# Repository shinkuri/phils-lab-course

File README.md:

# Learning PCB Design 
## Phil's Lab #11

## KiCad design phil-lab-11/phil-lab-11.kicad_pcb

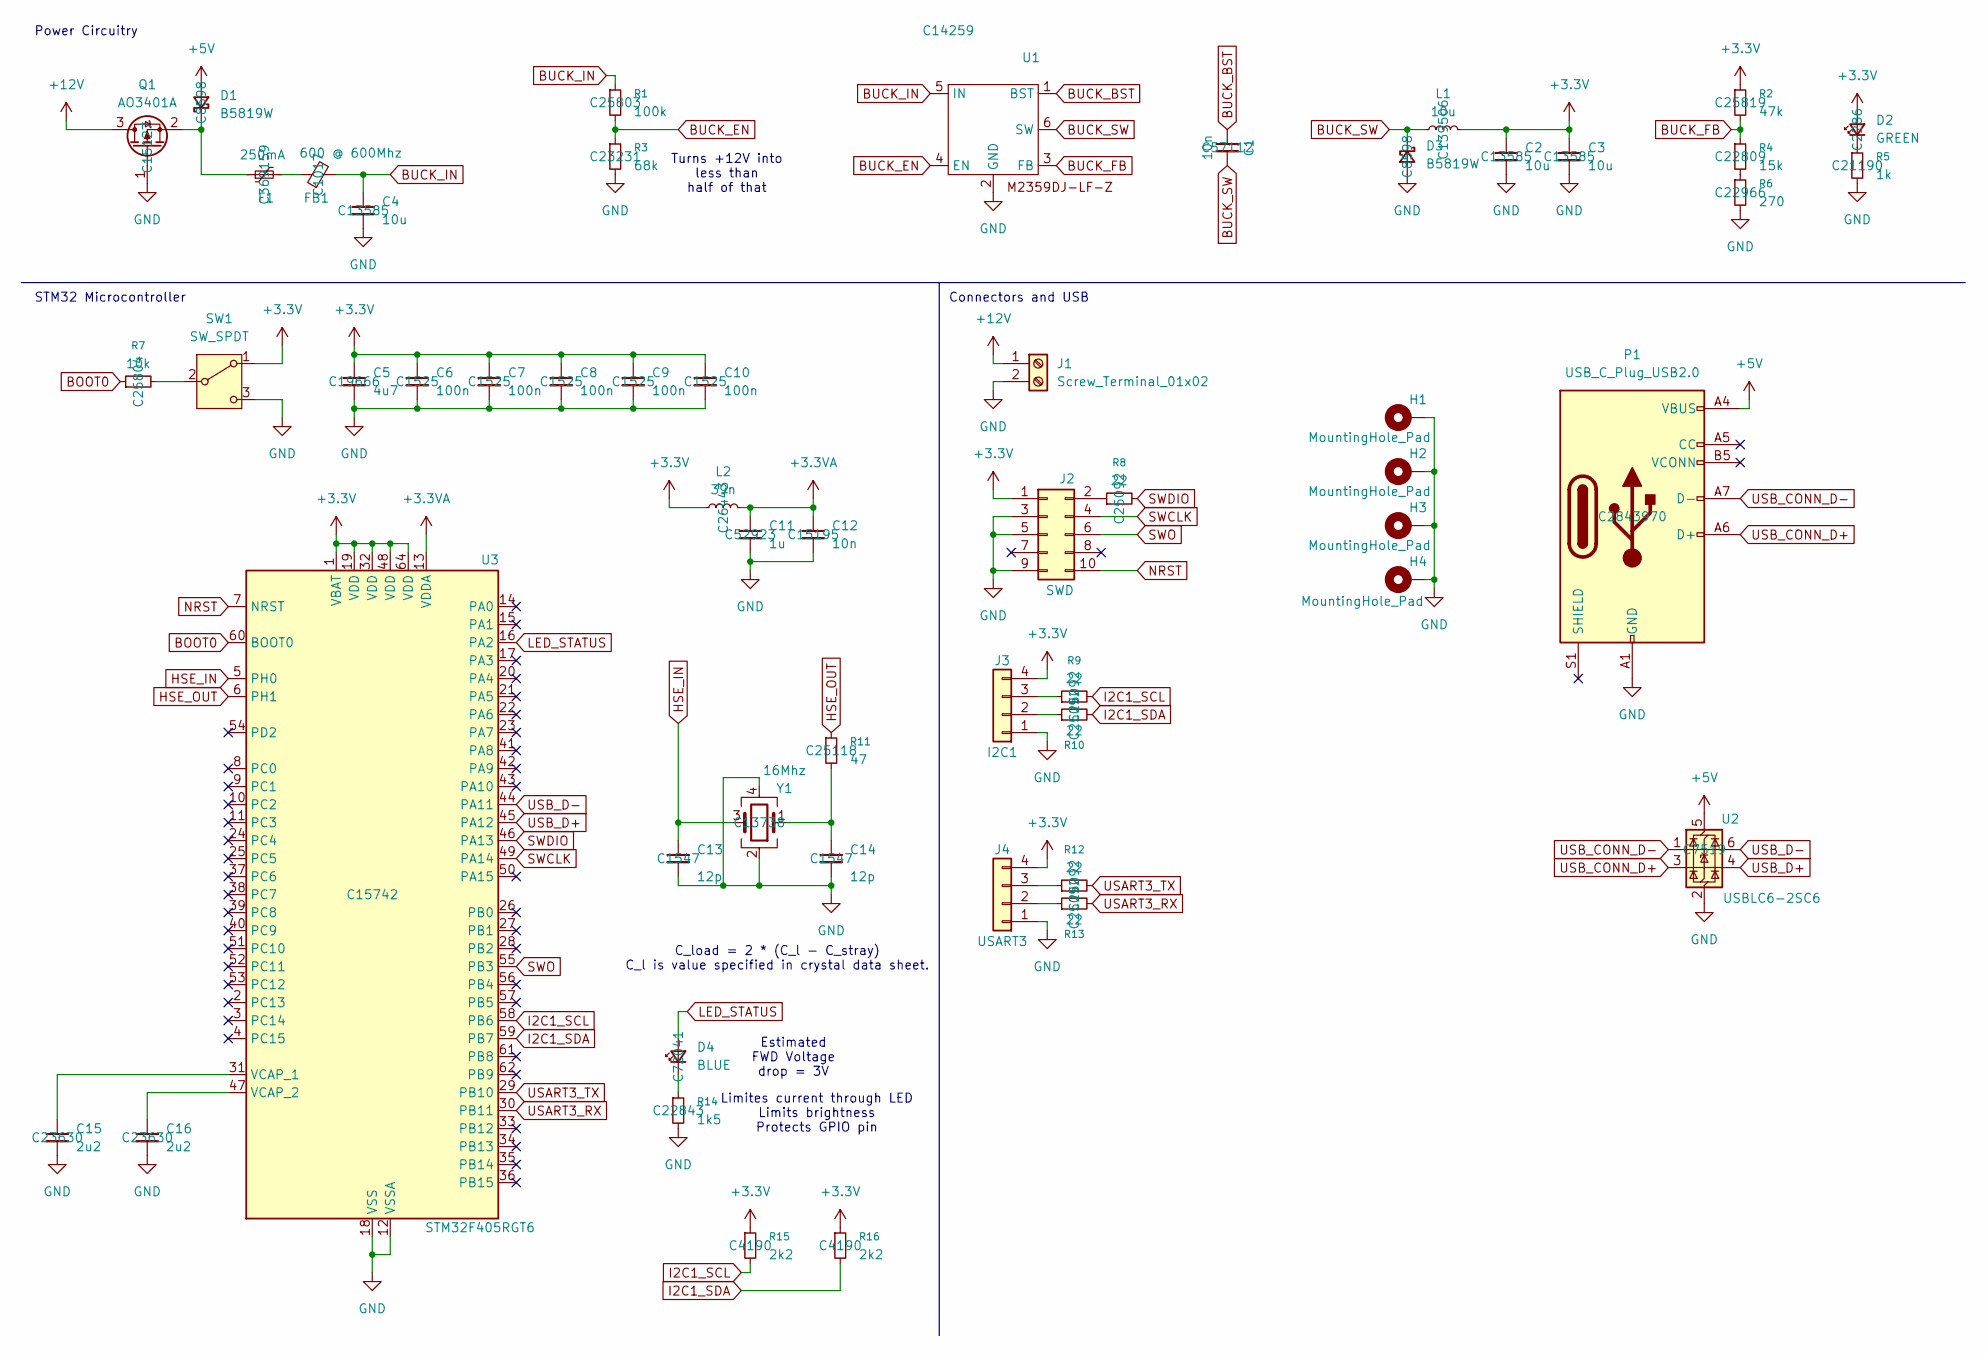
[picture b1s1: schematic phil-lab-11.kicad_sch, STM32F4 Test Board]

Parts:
C1: 10n; C_0603_1608Metric; LCSC Part C57112
C2, C3, C4: 10u; C_1206_3216Metric; LCSC Part C13585
C5: 4u7; C_0603_1608Metric; LCSC Part C19666
C6, C7, C8, C9, C10: 100n; C_0402_1005Metric; LCSC Part C1525
C11: 1u; C_0402_1005Metric; LCSC Part C52923
C12: 10n; C_0402_1005Metric; LCSC Part C15195
C13, C14: 12p; C_0402_1005Metric; LCSC Part C1547
C15, C16: 2u2; C_0603_1608Metric; LCSC Part C23630
D1, D3: B5819W; D_SOD-123; LCSC Part C8598
D2: GREEN; LED_0603_1608Metric; LCSC Part C2286
D4: BLUE; LED_0603_1608Metric; LCSC Part C72041
F1: 250mA; Fuse_1206_3216Metric; LCSC Part C369159
FB1: 600 @ 600Mhz; L_0805_2012Metric; LCSC Part C1017
H1, H2, H3, H4: MountingHole_Pad; MountingHole_4.3mm_M4_Pad_Via
J1: Screw_Terminal_01x02; TerminalBlock_Phoenix_PT-1,5-2-3.5-H_1x02_P3.50mm_Horizontal
J2: SWD; PinHeader_2x05_P1.27mm_Vertical_SMD
J3: I2C1; PinHeader_1x04_P1.27mm_Vertical_SMD_Pin1Right
J4: USART3; PinHeader_1x04_P1.27mm_Vertical_SMD_Pin1Right
L1: 10u; L_Sunlord_MWSA0503S; LCSC Part C139506
L2: 39n; L_0402_1005Metric; LCSC Part C26443
P1: USB_C_Plug_USB2.0; USB_C_Receptacle_G-Switch_GT-USB-7051x; LCSC Part C2843970
Q1: AO3401A; SOT-23; LCSC Part C15127
R1: 100k; R_0603_1608Metric; LCSC Part C25803
R2: 47k; R_0603_1608Metric; LCSC Part C25819
R3: 68k; R_0603_1608Metric; LCSC Part C23231
R4: 15k; R_0603_1608Metric; LCSC Part C22809
R5: 1k; R_0603_1608Metric; LCSC Part C21190
R6: 270; R_0603_1608Metric; LCSC Part C22966
R7: 10k; R_0402_1005Metric; LCSC Part C25804
R8, R9, R10, R12, R13: 22; R_0402_1005Metric; LCSC Part C25092
R11: 47; R_0402_1005Metric; LCSC Part C25118
R14: 1k5; R_0603_1608Metric; LCSC Part C22843
R15, R16: 2k2; R_0603_1608Metric; LCSC Part C4190
SW1: SW_SPDT; SW_SPDT_PCM12
U1: SOT-23-6; LCSC Part C14259
U2: USBLC6-2SC6; SOT-23-6; LCSC Part C7519
U3: STM32F405RGT6; LQFP-64_10x10mm_P0.5mm; LCSC Part C15742
Y1: 16Mhz; Crystal_SMD_3225-4Pin_3.2x2.5mm; LCSC Part C13738

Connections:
+3.3V: C2.1, C3.1, C5.1, C6.1, C7.1, C8.1, C9.1, C10.1, D2.2 (A), J2.1, J3.4, J4.4, L1.2, L2.1, R2.1, R15.1, R16.1, SW1.1 (A), U3.1 (VBAT), U3.19 (VDD), U3.32 (VDD), U3.48 (VDD), U3.64 (VDD)
+3.3VA: C11.1, C12.1, L2.2, U3.13 (VDDA)
+5V: D1.2 (A), P1.A4 (VBUS), P1.A9 (VBUS), P1.B4 (VBUS), P1.B9 (VBUS), U2.5 (VBUS)
+12V: J1.1, Q1.3 (D)
BOOT0: R7.1, U3.60 (BOOT0)
BUCK_BST: C1.1, U1.1 (BST)
BUCK_EN: R1.2, R3.1, U1.4 (EN)
BUCK_FB: R2.2, R4.1, U1.3 (FB)
BUCK_IN: C4.1, FB1.2, R1.1, U1.5 (IN)
BUCK_SW: C1.2, D3.1 (K), L1.1, U1.6 (SW)
GND: C2.2, C3.2, C4.2, C5.2, C6.2, C7.2, C8.2, C9.2, C10.2, C11.2, C12.2, C13.2, C14.2, C15.2, C16.2, D3.2 (A), H1.1, H2.1, H3.1, H4.1, J1.2, J2.3, J2.5, J2.9, J3.1, J4.1, P1.A1 (GND), P1.A12 (GND), P1.B1 (GND), P1.B12 (GND), Q1.1 (G), R3.2, R5.2, R6.2, R14.2, SW1.3 (C), U1.2 (GND), U2.2 (GND), U3.12 (VSSA), U3.18 (VSS), U3.63 (VSS), Y1.2, Y1.4
HSE_IN: C13.1, U3.5 (PH0), Y1.3
HSE_OUT: R11.1, U3.6 (PH1)
I2C1_SCL: R9.2, R15.2, U3.58 (PB6)
I2C1_SDA: R10.2, R16.2, U3.59 (PB7)
LED_STATUS: D4.2 (A), U3.16 (PA2)
NRST: J2.10, U3.7 (NRST)
unnamed: C14.1, R11.2, Y1.1
unnamed: D1.1 (K), F1.1, Q1.2 (S)
unnamed: D2.1 (K), R5.1
unnamed: D4.1 (K), R14.1
unnamed: F1.2, FB1.1
unnamed: J2.2, R8.1
unnamed: J3.2, R10.1
unnamed: J3.3, R9.1
unnamed: J4.2, R13.1
unnamed: J4.3, R12.1
unnamed: R4.2, R6.1
unnamed: R7.2, SW1.2 (B)
unnamed: C15.1, U3.31 (VCAP_1)
unnamed: C16.1, U3.47 (VCAP_2)
SWCLK: J2.4, U3.49 (PA14)
SWDIO: R8.2, U3.46 (PA13)
SWO: J2.6, U3.55 (PB3)
USART3_RX: R13.2, U3.30 (PB11)
USART3_TX: R12.2, U3.29 (PB10)
USB_CONN_D+: P1.A6 (D+), U2.3 (I/O2)
USB_CONN_D-: P1.A7 (D-), U2.1 (I/O1)
USB_D+: U2.4 (I/O2), U3.45 (PA12)
USB_D-: U2.6 (I/O1), U3.44 (PA11)

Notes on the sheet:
Estimated FWD Voltage drop = 3V
STM32 Microcontroller
Connectors and USB
Turns +12V into less than half of that
Power Circuitry
C_load = 2 * (C_l - C_stray) C_l is value specified in crystal data sheet.
Limites current through LED Limits brightness Protects GPIO pin

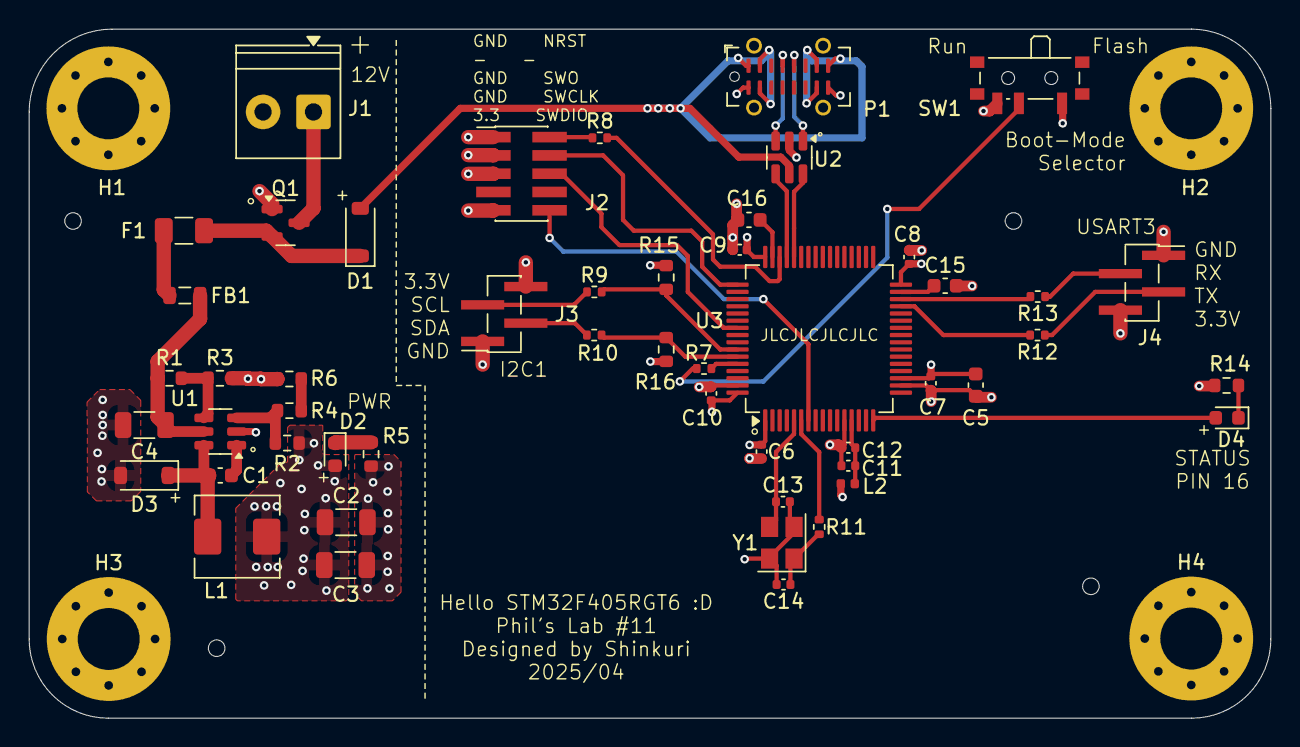
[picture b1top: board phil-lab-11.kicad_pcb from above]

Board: 4 copper layers, 86.2 x 47.9 mm, 55 parts (0 on the bottom side), 40 nets.

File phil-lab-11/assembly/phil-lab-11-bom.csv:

Comment,Designator,Footprint,LCSC Part #
"10n Unpolarized capacitor, small symbol",C1,C_0603_1608Metric,C57112
"10u Unpolarized capacitor, small symbol","C2,C3,C4",C_1206_3216Metric,C13585
"4u7 Unpolarized capacitor, small symbol",C5,C_0603_1608Metric,C19666
"100n Unpolarized capacitor, small symbol","C6,C7,C8,C9,C10",C_0402_1005Metric,C1525
"1u Unpolarized capacitor, small symbol",C11,C_0402_1005Metric,C52923
"10n Unpolarized capacitor, small symbol",C12,C_0402_1005Metric,C15195
"12p Unpolarized capacitor, small symbol","C13,C14",C_0402_1005Metric,C1547
"2u2 Unpolarized capacitor, small symbol","C15,C16",C_0603_1608Metric,C23630
"B5819W Schottky diode, small symbol","D1,D3",D_SOD-123,C8598
"GREEN Light emitting diode, small symbol",D2,LED_0603_1608Metric,C2286
"BLUE Light emitting diode, small symbol",D4,LED_0603_1608Metric,C72041
"250mA Resettable fuse, polymeric positive temperature coefficient, small symbol",F1,Fuse_1206_3216Metric,C369159
"600 @ 600Mhz Ferrite bead, small symbol",FB1,L_0805_2012Metric,C1017
"Screw_Terminal_01x02 Generic screw terminal, single row, 01x02, script generated (kicad-library-utils/schlib/autogen/connector/)",J1,"TerminalBlock_Phoenix_PT-1,5-2-3.5-H_1x02_P3.50mm_Horizontal",
"SWD Generic connector, double row, 02x05, odd/even pin numbering scheme (row 1 odd numbers, row 2 even numbers), script generated (kicad-library-utils/schlib/autogen/connector/)",J2,PinHeader_2x05_P1.27mm_Vertical_SMD,
"I2C1 Generic connector, single row, 01x04, script generated (kicad-library-utils/schlib/autogen/connector/)",J3,PinHeader_1x04_P1.27mm_Vertical_SMD_Pin1Right,
"USART3 Generic connector, single row, 01x04, script generated (kicad-library-utils/schlib/autogen/connector/)",J4,PinHeader_1x04_P1.27mm_Vertical_SMD_Pin1Right,
"10u Inductor, small symbol",L1,L_Sunlord_MWSA0503S,C139506
"39n Inductor, small symbol",L2,L_0402_1005Metric,C26443
USB_C_Plug_USB2.0 USB 2.0-only Type-C Plug connector,P1,USB_C_Receptacle_G-Switch_GT-USB-7051x,C2843970
"AO3401A -4.0A Id, -30V Vds, P-Channel MOSFET, SOT-23",Q1,SOT-23,C15127 
"100k Resistor, small symbol",R1,R_0603_1608Metric,C25803
"47k Resistor, small symbol",R2,R_0603_1608Metric,C25819
"68k Resistor, small symbol",R3,R_0603_1608Metric,C23231
"15k Resistor, small symbol",R4,R_0603_1608Metric,C22809
"1k Resistor, small symbol",R5,R_0603_1608Metric,C21190 
"270 Resistor, small symbol",R6,R_0603_1608Metric,C22966
"10k Resistor, small symbol",R7,R_0402_1005Metric,C25804
"22 Resistor, small symbol","R8,R9,R10,R12,R13",R_0402_1005Metric,C25092
"47 Resistor, small symbol",R11,R_0402_1005Metric,C25118
"1k5 Resistor, small symbol",R14,R_0603_1608Metric,C22843
"2k2 Resistor, small symbol","R15,R16",R_0603_1608Metric,C4190
"SW_SPDT Switch, single pole double throw",SW1,SW_SPDT_PCM12,
~ ,U1,SOT-23-6,C14259
"USBLC6-2SC6 Very low capacitance ESD protection diode, 2 data-line, SOT-23-6",U2,SOT-23-6,C7519
"STM32F405RGT6 STMicroelectronics Arm Cortex-M4 MCU, 1024KB flash, 192KB RAM, 168 MHz, 1.8-3.6V, 51 GPIO, LQFP64",U3,LQFP-64_10x10mm_P0.5mm,C15742
"16Mhz Four pin crystal, GND on pins 2 and 4",Y1,Crystal_SMD_3225-4Pin_3.2x2.5mm,C13738

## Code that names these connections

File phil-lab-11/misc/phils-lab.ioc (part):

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Mcu.Name=STM32F405RGTx
Mcu.Package=LQFP64
Mcu.UserName=STM32F405RGTx
PA11.Mode=Device_Only
PA11.Signal=USB_OTG_FS_DM
PA12.Mode=Device_Only
PA12.Signal=USB_OTG_FS_DP
PA13.Mode=Trace_Asynchronous_SW
PA13.Signal=SYS_JTMS-SWDIO
PA14.Mode=Trace_Asynchronous_SW
PA14.Signal=SYS_JTCK-SWCLK
PB10.Mode=Asynchronous
PB10.Signal=USART3_TX
PB11.Mode=Asynchronous
PB11.Signal=USART3_RX
PB3.Mode=Trace_Asynchronous_SW
PB3.Signal=SYS_JTDO-SWO
PB6.Mode=I2C
PB6.Signal=I2C1_SCL
PB7.Mode=I2C
PB7.Signal=I2C1_SDA
PH0-OSC_IN.Mode=HSE-External-Oscillator
PH0-OSC_IN.Signal=RCC_OSC_IN
PH1-OSC_OUT.Mode=HSE-External-Oscillator
PH1-OSC_OUT.Signal=RCC_OSC_OUT
RCC.HSE_VALUE=25000000
RCC.SYSCLKFreq_VALUE=16000000
board=custom

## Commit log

2025-04-29 ignoring kicad backup stuff
2025-04-29 phils lab 11 done yippie
2025-04-29 pretty pictures
2025-04-29 make site look nicer
2025-04-29 paths thehe
